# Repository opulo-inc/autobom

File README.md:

# AutoBOM

AutoBOM is a Bill of Materials exporting and rendering tool. It does:

- Automatic exporting of manufacturing filetypes for 3D models, circuit boards, and wire harnesses
- Generating a shareable Bill of Materials webpage with renders of all parts
- Standardization of a Bill of Materials format

AutoBOM is a command line tool and can be run locally, but is meant to be used as a Github Action for automatic exporting and rendering of a BoM for hardware releases.

It is an effort to formalize and standardize the smattering of automatic export and render tools developed as part of the [LumenPnP project](https://github.com/opulo-inc/lumenpnp).

This is still *heavily* in beta. There are bugs abound. Very likely any bug reports will become pretty out of date pretty quickly at this stage, but feature requests are welcome!

There are only a handful of CAD packages that we can support, given that all this exporting needs to run headless and automatically. Here is the list of planned packages we will support:

- [x] FreeCAD
- [ ] OpenSCAD
- [x] KiCAD
- [x] WireViz

## Usage

### Running in Github Actions

1. In your hardware repo root, add `autobom.json` and a BOM file (see [Config](#config) below).
2. Copy [`examples/autobom.workflow.yaml`](examples/autobom.workflow.yaml) to `.github/workflows/autobom.yaml` (or paste the snippet below).
3. Push a release or run the workflow via **workflow_dispatch**. AutoBOM uploads an `Autobom` artifact containing exports, renders, `index.html`, and `manifest.json`.

Each Action run builds the FreeCAD, KiCAD, and WireViz Docker images from the Dockerfiles in this repo (slow the first time / when Dockerfiles change; simple and self-contained).

```yaml
name: AutoBOM

on:
  release:
    types: [published]
  workflow_dispatch:

jobs:
  autobom:
    runs-on: ubuntu-latest
    steps:
      - uses: actions/checkout@v4
      - uses: opulo-inc/autobom@v0.2.0
```

Pin a release tag (`@v0.2.0`) rather than `@main` for reproducible builds.

### Config

Place **`autobom.json`** in the root of your hardware repository. AutoBOM reads this file first, then loads the BOM at `bom_path`.

#### `autobom.json` reference

```json
{
  "source_url": "https://github.com/org/your-hardware-repo",
  "bom_path": "bom.json",
  "mcad": {
    "export": "step",
    "render": "src",
    "path": "mcad"
  },
  "ecad": {
    "export": "gerber",
    "render": "src",
    "path": "ecad"
  },
  "wcad": {
    "export": "svg",
    "path": "wcad"
  },
  "site": {
    "colors": {
      "primary": "daa520",
      "secondary": "af8000"
    }
  }
}
```

| Key | Required | Description |
|-----|----------|-------------|
| `source_url` | **yes** | Base URL of the hardware repo (no trailing slash). Used in the generated BOM page header and to build GitHub `blob/<sha>/…` links when `render` is `"src"`. |
| `bom_path` | **yes** | Path to the BOM JSON file, relative to the hardware repo root (e.g. `"bom.json"` or `"docs/bom.json"`). |
| `mcad` | **yes** | Defaults for mechanical CAD parts (`type: "mcad"` in the BOM). See below. |
| `ecad` | **yes** | Defaults for electronics CAD parts (`type: "ecad"` in the BOM). See below. |
| `wcad` | no | Defaults for wire harnesses (`type: "wcad"` in the BOM). See below. |
| `site` | **yes** | Options for the generated BOM webpage. See below. |
| `strict` | no | Default `false`. If `true`, the job exits non-zero when **any** part is missing or fails to export. If `false`, those are logged as warnings and the `autobom/` output is still produced. `optional` on a part does not change this. |

##### `mcad`

Controls mechanical parts (FreeCAD `.FCStd`, OpenSCAD `.scad`).

| Key | Required | Default | Description |
|-----|----------|---------|-------------|
| `export` | **yes** | — | Which manufacturing export to record in `manifest.json` for each mcad part. Allowed: `"step"`, `"stl"`. (The FreeCAD render engine still runs the full export/render pass; this field selects which file path is written into the part’s `export` entry in the manifest.) |
| `render` | **yes** | — | How the BOM page should prefer to display this part. See [Render modes](#render-modes) below. |
| `path` | no | *(whole repo)* | Subdirectory (relative to repo root) to search for source files. If omitted, AutoBOM walks the entire repository. Example: `"pnp/cad"`. |

##### `ecad`

Controls electronics parts (KiCAD projects with a `.kicad_pro` file).

| Key | Required | Default | Description |
|-----|----------|---------|-------------|
| `export` | **yes** | — | Intended manufacturing export mode. Conventional value: `"gerber"`. Today KiBot always runs the outputs defined in AutoBOM’s `render/config.kibot.yaml` (gerbers, plots, BOM CSV, etc.) regardless of this string; keep `"gerber"` for forward compatibility. |
| `render` | **yes** | — | How the BOM page should prefer to display this part. See [Render modes](#render-modes) below. |
| `path` | no | *(whole repo)* | Subdirectory (relative to repo root) to search for KiCAD projects. If omitted, AutoBOM walks the entire repository. Example: `"pnp/pcb"`. |

##### `wcad`

Controls wire harnesses (WireViz `.yml` / `.yaml`). There is no interactive source viewer: the BOM page always shows the PNG WireViz writes.

Harness YAML is matched by filename stem. If the BOM name ends in `-harness` or `-cable` and no exact `{name}.yml` exists, AutoBOM also looks for the stem with that suffix stripped (`pump1-harness` → `pump1.yml`).

| Key | Required | Default | Description |
|-----|----------|---------|-------------|
| `export` | no | `"svg"` | Which WireViz output to record in `manifest.json`. Allowed: `"svg"`, `"png"`. WireViz still writes both (plus `.html` / `.gv` when present) under `export/<name>/`; the site preview is always `export/<name>.png`. |
| `path` | no | *(whole repo)* | Subdirectory to search for WireViz YAML. Strongly recommended so other `.yml` files are not treated as harnesses. Example: `"src/CHA"`. |

##### `site`

| Key | Required | Default | Description |
|-----|----------|---------|-------------|
| `colors` | no | see below | Theme colors for the generated BOM page. Hex values **without** a leading `#`. |
| `colors.primary` | no | `"daa520"` | Primary accent color. |
| `colors.secondary` | no | `"af8000"` | Secondary accent color. |

`site` itself must be present (even as `{}`). Color keys are accepted and merged with defaults; full CSS theming from these values is still evolving.

##### Render modes

Used by `mcad.render` and `ecad.render` (and by per-part overrides in the BOM). **WCAD ignores `render`:** WireViz has no interactive source viewer, so harnesses always use the exported PNG.

| Value | Behavior |
|-------|----------|
| `"src"` | Embed an interactive viewer from GitHub raw (`raw.githubusercontent.com` → the source `.FCStd` / `.kicad_pcb` at the build commit). Shows the local PNG with a “Loading source…” toast until the viewer is ready. Offline, stays on the PNG. |
| `"img"` | Show the local preview PNG from the artifact (`export/<name>.png` for mcad, `export/<name>/<name>-top.png` for ecad). |
| *(any other string)* | Treated as a custom image URL/path and used as the part’s `img_path` (useful for hosting a pre-rendered preview elsewhere). |

Any part in `bom.json` may set its own `"render"` or `"export"` field to override the matching `mcad` / `ecad` / `wcad` default for that part only.

---

#### `bom.json` (path from `bom_path`)

```json
{
  "name": "MyProduct",
  "parts": [
    {
      "name": "my-bracket",
      "quantity": 2,
      "type": "mcad",
      "optional": false,
      "source": "https://example.com",
      "notes": ""
    },
    {
      "name": "main-board",
      "quantity": 1,
      "type": "ecad",
      "optional": false,
      "source": "https://example.com",
      "notes": "",
      "render": "img",
      "export": "gerber"
    }
  ]
}
```

| Key | Required | Description |
|-----|----------|-------------|
| `name` | **yes** | Product name shown on the BOM page and in `manifest.json`. |
| `parts` | **yes** | Array of part objects (see below). |

The page title / `manifest.version` is **not** set in `bom.json`. It comes from git:

- Local run or `workflow_dispatch`: short commit hash
- `release` event: the release tag (e.g. `v4.2.0`)

##### Part object

| Key | Required | Description |
|-----|----------|-------------|
| `name` | **yes** | Must match the FreeCAD/OpenSCAD filename stem (e.g. `my-bracket` → `my-bracket.FCStd`), the KiCAD project name (directory containing `my-bracket.kicad_pro`), or the WireViz YAML stem (`pump1.yml`, or `pump1-harness` matching `pump1.yml` as described under `wcad`). |
| `quantity` | **yes** | Count shown in the BOM table. |
| `type` | **yes** | `"mcad"` (FreeCAD / OpenSCAD), `"ecad"` (KiCAD), `"wcad"` (WireViz), `"misc"` (no CAD export; optional `render` URL for a preview image). |
| `optional` | no | Informational only (shown on the BOM page). Does **not** change whether AutoBOM treats the part as required. |
| `source` | no | Link(s) shown in the BOM table. A string, or an array of strings (`["https://a", "https://b"]`) which renders as Link 1, Link 2, … |
| `notes` | no | Free-text note shown in the BOM table. |
| `render` | no | Overrides `mcad.render` / `ecad.render` for this part only. Same values as [Render modes](#render-modes). Ignored for `"wcad"`. |
| `export` | no | Overrides `mcad.export` / `ecad.export` / `wcad.export` for this part only. |

CAD sources are searched under `mcad.path` / `ecad.path` / `wcad.path` when set; otherwise the whole repo.

See also [opulo-inc/example-autobom-project](https://github.com/opulo-inc/example-autobom-project).

### Running local

Requires Docker Desktop (or equivalent) running. From your hardware repo root:

```bash
uv run --project /path/to/autobom/repo autobom
```

Locally, `autobom` starts the FreeCAD/KiCAD/WireViz containers if they aren’t already up, waits for ports 9001/9002/9003, runs the build, then stops containers it started. On Apple Silicon it uses `docker-compose-local.yaml`; elsewhere `docker-compose.yaml`.

- If engines are already running, they are reused and left up afterward.
- To keep engines you started (faster re-runs): `AUTOBOM_KEEP_ENGINES=1 uv run --project /path/to/autobom/repo autobom`

Under GitHub Actions, `action.yaml` owns container start/stop; the CLI does not manage Docker there.

You'll get an `autobom/` folder in the hardware repo root with exports and `index.html`.

To export STEP from every FreeCAD file in a tree:

    `uv run --project /path/to/autobom/repo export-freecad`

## References and Dependencies

- [KiCanvas](https://kicanvas.org/)
- [Online3DViewer](https://github.com/kovacsv/Online3DViewer)
- [FreeCAD](https://github.com/FreeCAD/FreeCAD)
- [KiCAD](https://gitlab.com/kicad/code/kicad)
- [KiBot](https://github.com/INTI-CMNB/KiBot)
- [WireViz](https://github.com/formatc1702/WireViz)
- [OpenSCAD](https://github.com/openscad/openscad/)

## DEV

Here's a rough breakdown of what's in this repo

- `./render` contains scripts, Dockerfiles, and other assets used for spinning up the render engines. These are the docker containers whose sole purpose is to do the actual work of exporting files from various CAD packages.
  - `Dockerfile-freecad-gha` defines the container for the freecad "render engine" when running in Github Actions (x86_64 FreeCAD AppImage).
  - `Dockerfile-freecad-local` is for Apple Silicon local testing.
  - `Dockerfile-kicad` runs KiBot against a whole KiCAD project directory.
  - `Dockerfile-wireviz` runs WireViz (Graphviz) against a harness YAML directory.
  - `./docker-compose-local.yaml` builds images locally for Mac ARM.
  - `./docker-compose.yaml` builds images for the Github Action (x86 FreeCAD + KiCAD + WireViz).
- `./renderQueue` is a folder that the render engine docker containers use to exchange source/export files with the host.
- `./src` is where all the Autobom python source exists. This is what generates the website, parses the bom and config files, finds the source files, and makes decisions about what files get rendered where.
- `./action.yaml` is the composite Github Action entrypoint.
- Builder ↔ renderers talk over TCP (JSON length-prefixed messages) on ports 9001 (MCAD), 9002 (ECAD), and 9003 (WCAD).

TODO:
- openscad has not been fully tested in CI
- logging is messy
- generally needs a refactor, chunks of logic have moved around with reckless abandon, now that things are a bit more stable the general structure of the autobom python codebase needs a refresh

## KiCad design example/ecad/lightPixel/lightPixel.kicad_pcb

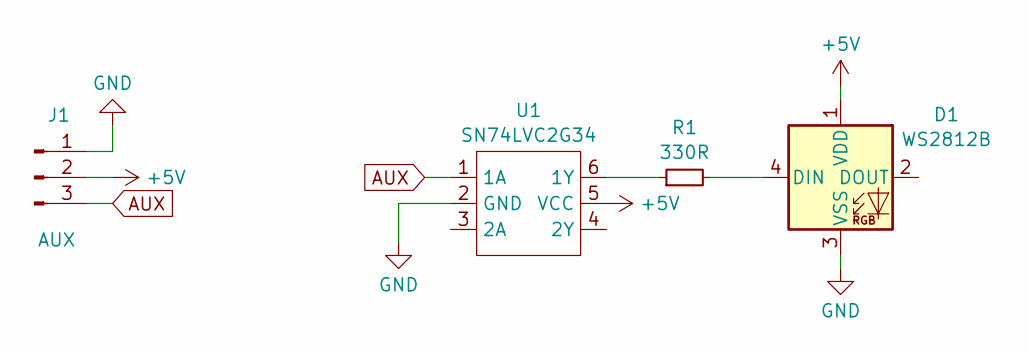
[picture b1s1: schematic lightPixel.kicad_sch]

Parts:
D1: WS2812B; LED_WS2812B_PLCC4_5.0x5.0mm_P3.2mm
J1: AUX; JST_PH_S3B-PH-SM4-TB_1x03-1MP_P2.00mm_Horizontal
R1: 330R; R_0805_2012Metric
U1: SN74LVC2G34; TSOT-23-6_HandSoldering

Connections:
+5V: D1.1 (VDD), J1.2, U1.5 (VCC)
AUX: J1.3, U1.1 (1A)
GND: D1.3 (VSS), J1.1, J1.MP, U1.2 (GND)
unnamed: D1.4 (DIN), R1.2
unnamed: R1.1, U1.6 (1Y)

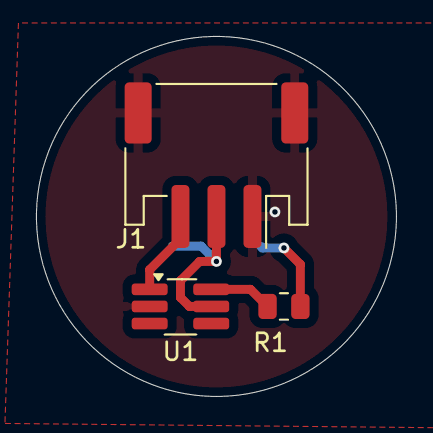
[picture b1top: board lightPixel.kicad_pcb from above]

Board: 2 copper layers, 20.0 x 20.0 mm, 4 parts (1 on the bottom side), 5 nets.

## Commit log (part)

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2024-06-03 fixes gitignore to allow src to be added
2024-06-03 adds some to readme
2024-06-03 more readme
2024-06-03 readme
2024-06-08 adds openscad support. cleans up logging.
2024-11-02 lots of changes
2024-11-03 testing a docker build
2024-11-03 the correct freecad architecture now
2024-11-03 tries to fix the old venv not being deleted
2024-11-13 first crack at getting all the render engines running in docker
2024-11-13 updates readme to describe the nightmare i have created
2024-12-01 insane refactor
2024-12-01 changes docker compose command
2024-12-01 fjdkflas
2024-12-01 trying githubs fancy way of handling env var
2024-12-01 switching to sed
2024-12-01 switches up dockerfiles so there's separate ones for different purposes
2024-12-01 adds uv to action
2024-12-01 removed old freecad dependency in mcad.py
2024-12-01 adds some debugging checks, removes cd
2024-12-01 sdksjdfkal
2024-12-01 tries to update permissions of files when deleting after copying
2024-12-01 adds official logging lib
2024-12-01 should log more now
2024-12-01 added more debuggint
2024-12-01 kitchen sink
2024-12-01 more debugging
2024-12-01 maybe the dumbest thing ive done
2024-12-01 holy smokes im almost there
2024-12-01 removing kicad deleting export from kicad/out when done just for testing
2024-12-01 cleanup, update readme
2024-12-01 moving docker-compose files back to root
2026-01-11 updates readme
